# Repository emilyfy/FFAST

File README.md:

# FFAST

## Introduction

The FFAST vehicle is a 1:10 scale RC car functioning as a test platform for testing dynamic motion planning and control algorithms. This repository contains the software developed throughout the project, including the source codes in the vehicle responsible for autonomous driving and executing maneuvers such as drifting and obstacle avoidance.

## Functionalities

The rear-wheel drive front steering vehicle is capable of driving with speed of up to 6 m/s forward and 3 m/s backwards and achieving steering angles of 30 degrees on either side. It achieves localization reasonably well using data from the Hall effect sensors on the motor as odometry, IMU, LIDAR and the camera on the Jetson developer kit with optic flow. It can be teleoperated or controlled by a software giving it navigation commands. An RF receiver on the vehicle stops vehicle operation when the remote transmitter is pressed, acting as an emergency kill switch.

## Organization

The repository is divided into several subfolders:
- doc  
Directory for instructions for developing the RC car platform and the detailed documentation of the project
- catkin_ws  
Catkin workspace containing the ROS packages that control the vehicle
- matlab_simulator  
MATLAB scripts for simulation of vehicle dynamics and execution of the maneuvers in simulation

## Getting Started

The [setup instructions](doc/setup_instructions.md) will get you a copy of the project up and running on your local machine for development and testing purposes. It has been developed for Linux, and no cross-compatibility effort has been made.

## Running the tests
Refer to the [test runs](doc/test_runs.md) for the commands to run the tests.

## Authors

* **Jordan Ford** - [jsford](https://github.com/jsford)
* **Emily Yunan** - [emilyfy](https://github.com/emilyfy)
* **Shihao Xu** - [FromVic](https://github.com/FromVic)

See also the list of [contributors](https://github.com/jsford/FFAST/contributors) who participated in this project.

## License

MIT License  
Copyright (C) 2017 Jordan Ford  
The Robotics Institute, Carnegie Mellon University

Permission is hereby granted, free of charge, to any person obtaining a copy of this software and associated documentation files (the "Software"), to deal in the Software without restriction, including without limitation the rights to use, copy, modify, merge, publish, distribute, sublicense, and/or sell copies of the Software, and to permit persons to whom the Software is furnished to do so, subject to the following conditions: The above copyright notice and this permission notice shall be included in all copies or substantial portions of the Software.

THE SOFTWARE IS PROVIDED "AS IS", WITHOUT WARRANTY OF ANY KIND, EXPRESS OR IMPLIED, INCLUDING BUT NOT LIMITED TO THE WARRANTIES OF MERCHANTABILITY, FITNESS FOR A PARTICULAR PURPOSE AND NONINFRINGEMENT. IN NO EVENT SHALL THE AUTHORS OR COPYRIGHT HOLDERS BE LIABLE FOR ANY CLAIM, DAMAGES OR OTHER LIABILITY, WHETHER IN AN ACTION OF CONTRACT, TORT OR OTHERWISE, ARISING FROM, OUT OF OR IN CONNECTION WITH THE SOFTWARE OR THE USE OR OTHER DEALINGS IN THE SOFTWARE.

## Acknowledgments

* Carnegie Mellon University 
* General Motors Research and Development

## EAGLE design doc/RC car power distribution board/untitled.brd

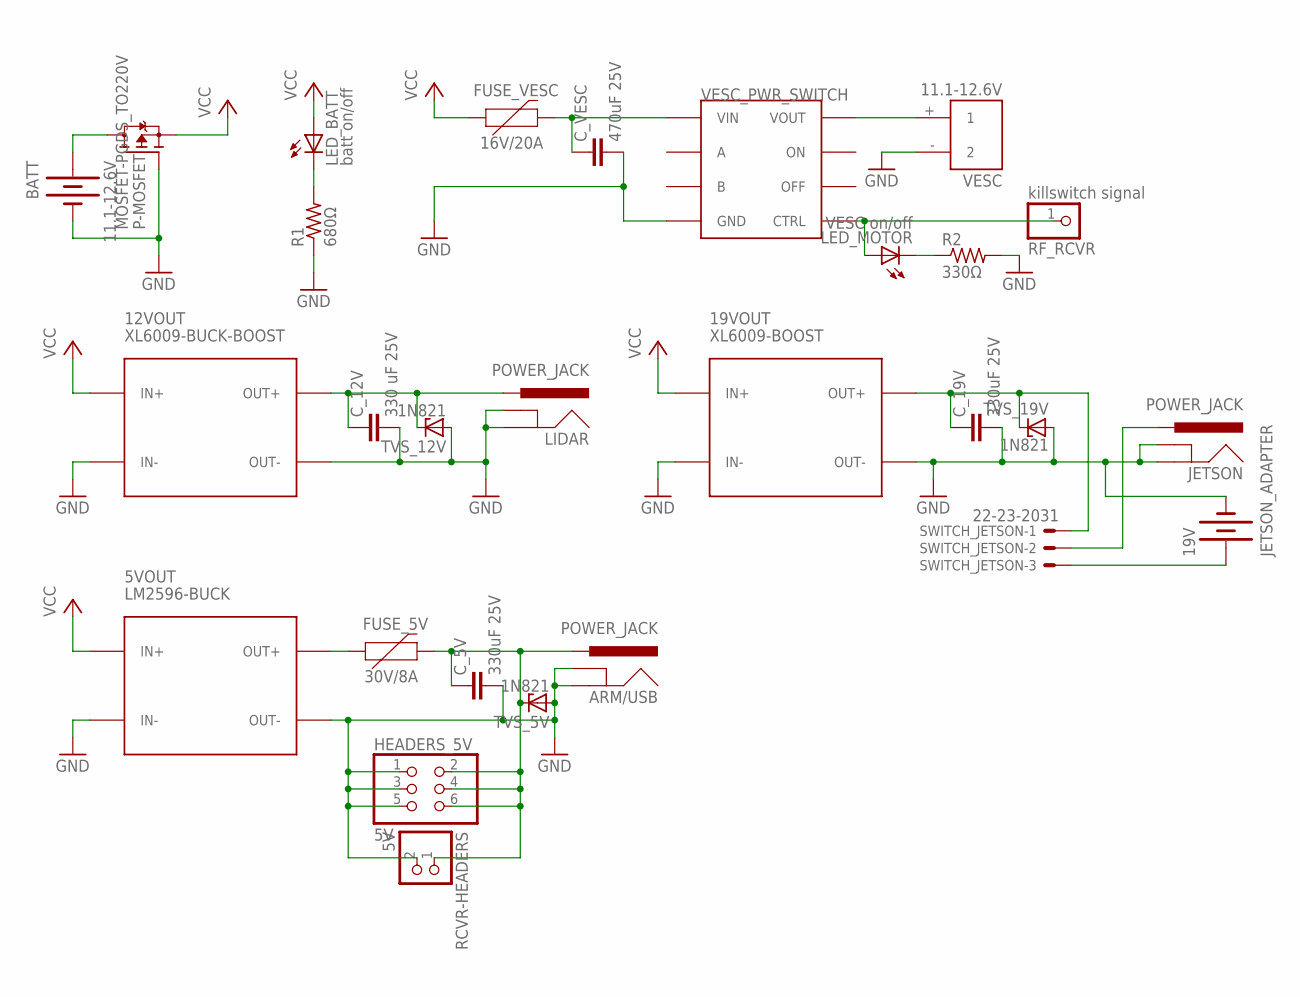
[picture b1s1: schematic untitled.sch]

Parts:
5VOUT: LM2596-BUCK
12VOUT: XL6009-BUCK-BOOST; BUCK-BOOST-XL6009
19VOUT: XL6009-BOOST
ARM/USB: POWER_JACK; POWER_JACK_PTH
BATT: 11.1-12.6V; XT60
C_5V, C_19V: 330uF 25V; C5B2.5
C_12V: 330 uF 25V; C5B2.5
C_VESC: 470uF 25V; C5B3
FUSE_5V: 30V/8A; PTH
FUSE_VESC: 16V/20A; PTH
HEADERS_5V: 5V; 2X03
JETSON: POWER_JACK; POWER_JACK_PTH
JETSON_ADAPTER: 19V; XT30
LED_BATT: batt on/off; LED_LD260
LED_MOTOR: VESC on/off; LED_LD260
LIDAR: POWER_JACK; POWER_JACK_PTH
P-MOSFET: MOSFET-PGDS_TO220V; TO220V
R1: 680Ω; 0204V
R2: 330Ω; 0204V
RCVR-HEADERS: 5V; 1X02
RF_RCVR: killswitch signal; 1X01
SWITCH_JETSON: 22-23-2031
TVS_5V, TVS_12V, TVS_19V: 1N821; DO35Z10
VESC: 11.1-12.6V; XT60_FEMALE
VESC_PWR_SWITCH: 0J9255

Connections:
12V: 12VOUT.OUT+, C_12V.1, LIDAR.PWR, TVS_12V.C
19V: 19VOUT.OUT+, C_19V.1, SWITCH_JETSON.1, TVS_19V.C
GND: 5VOUT.IN-, 5VOUT.OUT-, 12VOUT.IN-, 12VOUT.OUT-, 19VOUT.IN-, 19VOUT.OUT-, ARM/USB.GND, ARM/USB.GND2 (GNDBREAK), BATT.-, C_5V.2, C_12V.2, C_19V.2, C_VESC.2, HEADERS_5V.1, HEADERS_5V.3, HEADERS_5V.5, JETSON.GND, JETSON.GND2 (GNDBREAK), JETSON_ADAPTER.-, LIDAR.GND, LIDAR.GND2 (GNDBREAK), P-MOSFET.1 (G), R1.1, R2.2, RCVR-HEADERS.2, TVS_5V.A, TVS_12V.A, TVS_19V.A, VESC.- (2), VESC_PWR_SWITCH.GND, VESC_PWR_SWITCH.GND1 (GND), VESC_PWR_SWITCH.GND2 (GND), VESC_PWR_SWITCH.GND3 (GND), VESC_PWR_SWITCH.GND4 (GND), VESC_PWR_SWITCH.GND5 (GND), VESC_PWR_SWITCH.GND6 (GND), VESC_PWR_SWITCH.GND7 (GND)
unnamed: VESC.+ (1), VESC_PWR_SWITCH.VOUT1 (VOUT), VESC_PWR_SWITCH.VOUT2 (VOUT), VESC_PWR_SWITCH.VOUT3 (VOUT)
unnamed: JETSON_ADAPTER.+, SWITCH_JETSON.3
unnamed: LED_MOTOR.A, RF_RCVR.1, VESC_PWR_SWITCH.CTRL
unnamed: 5VOUT.OUT+, FUSE_5V.P$1 (1)
unnamed: LED_MOTOR.K (C), R2.1
unnamed: ARM/USB.PWR, C_5V.1, FUSE_5V.P$2 (2), HEADERS_5V.2, HEADERS_5V.4, HEADERS_5V.6, RCVR-HEADERS.1, TVS_5V.C
unnamed: LED_BATT.K (C), R1.2
unnamed: JETSON.PWR, SWITCH_JETSON.2
unnamed: BATT.+, P-MOSFET.2 (D)
VCC: 5VOUT.IN+, 12VOUT.IN+, 19VOUT.IN+, FUSE_VESC.P$1 (1), LED_BATT.A, P-MOSFET.3 (S)
VESC: C_VESC.1, FUSE_VESC.P$2 (2), VESC_PWR_SWITCH.VIN1 (VIN), VESC_PWR_SWITCH.VIN2 (VIN), VESC_PWR_SWITCH.VIN3 (VIN)

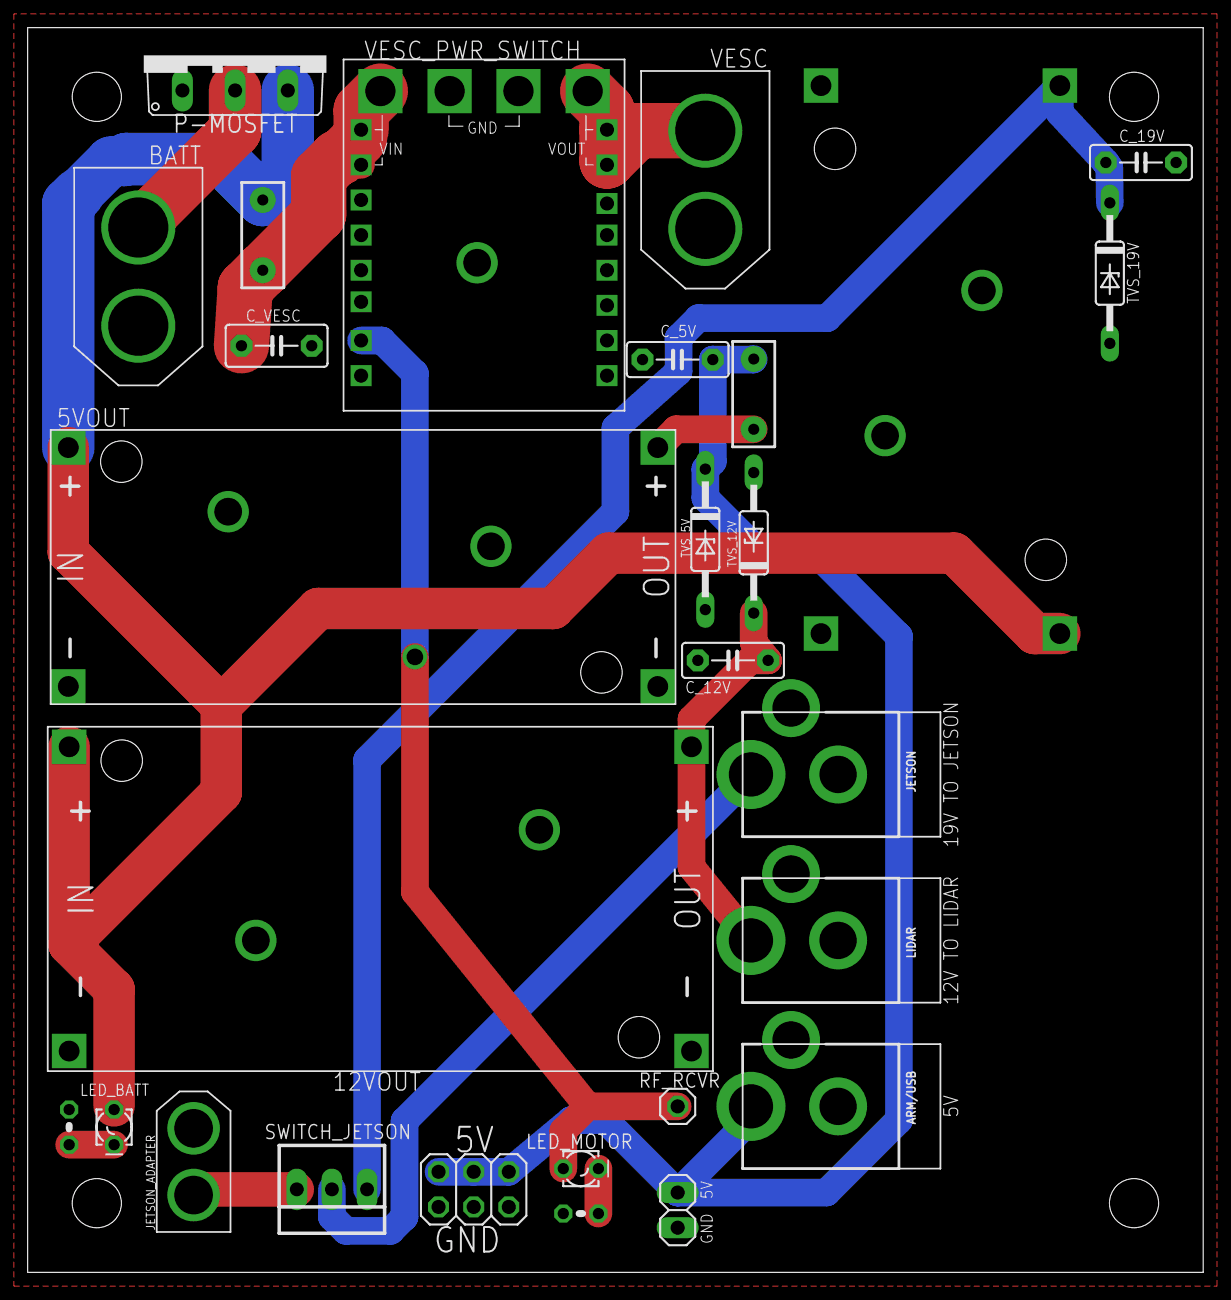
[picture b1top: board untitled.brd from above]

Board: 2 copper layers, 85.0 x 90.0 mm, 28 parts (1 on the bottom side), 14 nets.

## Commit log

2017-10-26 First commit of the FFAST autonomous driving project. Using pods and LCM. Right now the only pod is one I wrote to communicate with the VMU931 accelerometer.
2017-10-26 Fixing the lame code that came with the VMU931. Writing it in C++.
2017-10-26 Added udev rule for VMU931.
2017-11-14 Ditching the VMU931 because it sucks in linux. Figured out how to integrate Teensy with CMake and LCM! Pretty cool :D
2017-11-15 Added arduino libraries to read the Bosch accelerometer. Probably won't work if you don't have arduino and teensy installed at /usr/share/arduino. idk.
2017-11-18 Added README.md
2017-11-18 Fixed missing i2c code for teensy
2017-11-19 Added in PWMServo library for controlling the throttle and steering. Need to test on the car, but at least it builds.
2017-11-20 Added some code to test the servo outputs.
2017-11-20 Servo outputs for steering and throttle seem to be working. Need to figure out what the correct pulse width ranges are.
2017-12-05 Added vehicle singleton class with isr for estop. main should be running a sweep on the steering.
2018-01-12 Fixed VMU931, publishing data to LCM. Added listener executable to print IMU data from LCM.
2018-01-16 LIDAR works on Jetson TX2.
2018-01-18 Updated Teensy codes to send steering and throttle commands open loop, commands read from serial. Added lookup array and pod for serial communication to LCM interface.
2018-01-23 Cleaned up serial communications. Added serial_comms.h
2018-01-23 Created a global Vehicle. ISRs are now free functions with access to the global Vehicle.
2018-01-23 Changed global Vehicle to volatile. Had to make all its member functions volatile as well, but now its member variables don't have to be declared volatile. Idk. Looks better. Makes more sense to me.
2018-01-23 Fixed compile errors and warnings from teensy build. Had to create a static library with the C files and link it to the CPP executable so I could pass separate compile flags to each one. Pain in the 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
2018-01-23 Oops. Forgot to re-enable -Wall in the last commit. I am now. Don't mind me. Just making the commit history uglier.
2018-01-24 This commit is gonna tick off emily. I screwed up a lot of her code. Am now using COBS to send data from teensy to Jetson. Publishing it to LCM.
2018-01-24 Serial communication kind of works. Still not bulletproof. Using TinyPacks to serialize and COBS to frame data.
2018-01-26 Switched to ROS. Integrated teensy into ROS build system. This commit squashes several previous commits to the ROS branch.
2018-01-26 Added URDF and teensy codes with ROSSerial command. Able to send command to teensy and receive data back on ROS. About to start PID.
2018-01-31 Added EKF, laser scan matcher and joy listener to send command through joystick controller. Changed tf_publisher package name to tf_broadcaster and the tf_publisher node into static tf publisher. Als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
2018-02-13 Organized packages into categories. Added teensy_msgs package. tf on teensy failed cause message size is bigger than buffer. Added sysid package with 2 nodes, ramp steer (used in determining servo & 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
    Teensy is currently having the problems of going into hidraw mode
2018-02-27 Added VESC driver and interface, controlling both bldc motor and servo. Also modified other packages to be compatible. Removed teensy stuffs.
2018-03-01 Added jetson_gpio pkg for kill switch estop and tuned steering offset.
2018-03-12 Migrating from robot_pose_ekf to robot_localization.
2018-03-28 Using iLQR as planner. Added obstacle detector and optic flow to localization. Updated setup instructions (removed teensy and added vesc).
2018-04-12 Edited iLQR cost functions and tuned cost coefficient params.
2018-04-26 Added MATLAB codes.
2018-05-01 Added documentations.
2018-05-11 Added drift cornering from stationary controller.
2018-05-23 Edited laser_scan_matcher, trying to remove scan matching error when scan values NaN.
2018-05-23 Added navigation.
2018-05-23 TEB local planner for Indigo.
2018-06-30 Added navigation iLQR in MATLAB, but not working.

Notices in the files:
parts and their libraries:
SparkFun-Fuses: Licensing: Creative Commons ShareAlike 4.0 International - https://creativecommons.org/licenses/by-sa/4.0
